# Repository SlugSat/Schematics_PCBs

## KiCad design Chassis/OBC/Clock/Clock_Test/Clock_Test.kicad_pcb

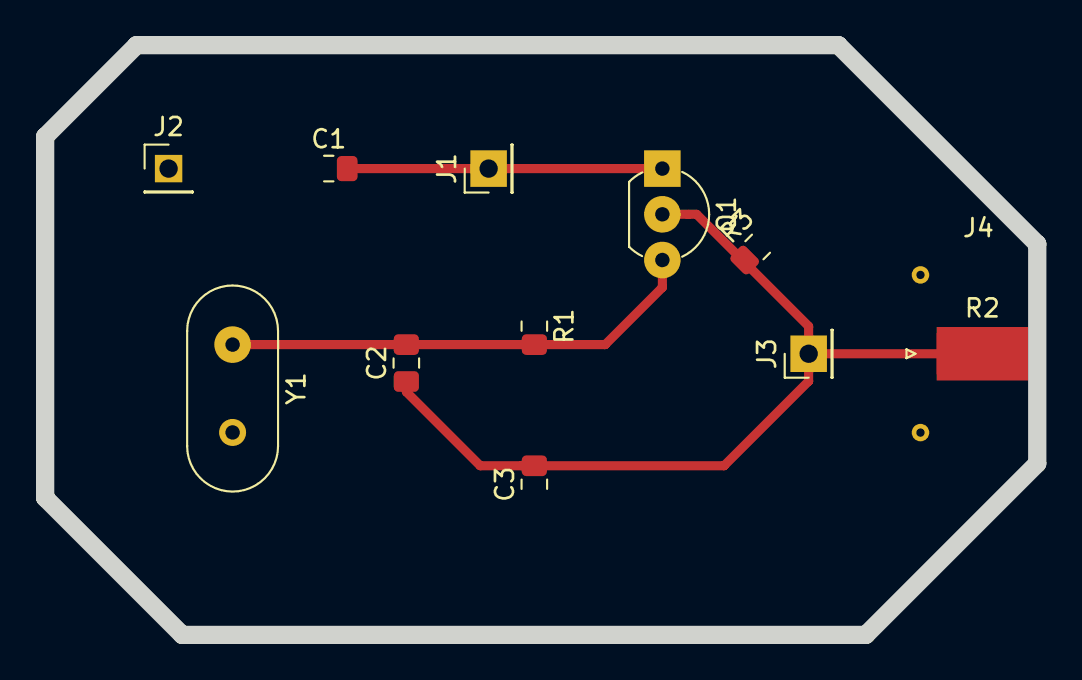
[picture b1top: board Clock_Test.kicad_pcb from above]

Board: 2 copper layers, 55.1 x 32.8 mm, 12 parts (0 on the bottom side), 4 nets.

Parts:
C1: 100 nF; C_0805_2012Metric_Pad1.15x1.40mm_HandSolder
C2: 33 pF; C_0805_2012Metric_Pad1.15x1.40mm_HandSolder
C3: 56 pF; C_0805_2012Metric_Pad1.15x1.40mm_HandSolder
J1: +1V8; PinHeader_1x01_P2.54mm_Vertical
J2, J3: Conn_01x01_Male; PinHeader_1x01_P2.54mm_Vertical
J4: Conn_Coaxial; SMA_Molex_73251-1153_EdgeMount_Horizontal
Q1: Q_NJFET_DSG; TO-92_Inline_Wide
R1: 1 M; R_0805_2012Metric_Pad1.15x1.40mm_HandSolder
R2: 50Oμs
R3: 1k; R_0805_2012Metric_Pad1.15x1.40mm_HandSolder
Y1: 10 MHz; Crystal_HC49-4H_Vertical

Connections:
/Gate: C2.2, Q1.3, R1.2, Y1.1
/Output: C2.1, C3.2, J3.1, J4.1, Q1.2, R2.1, R3.1
GND: C1.1, C3.1, J2.1, J4.2, R1.1, R3.2, Y1.2
unnamed: C1.2, J1.1, Q1.1

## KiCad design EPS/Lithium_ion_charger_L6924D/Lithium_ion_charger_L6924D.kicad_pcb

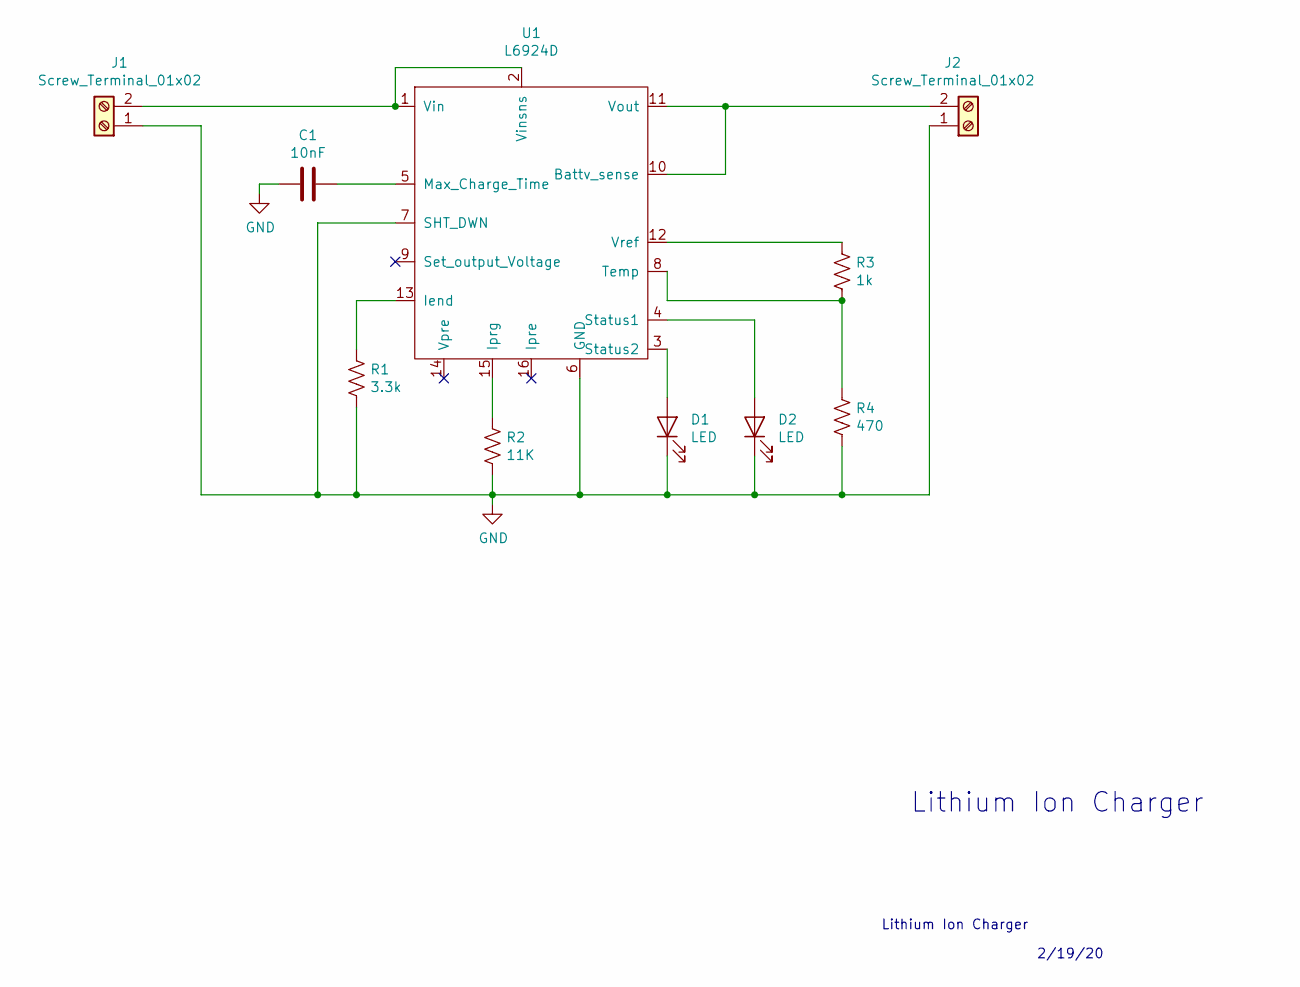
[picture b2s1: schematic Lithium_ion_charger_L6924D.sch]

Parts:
C1: 10nF; C_0805_2012Metric_Pad1.15x1.40mm_HandSolder
D1, D2: LED; LED_D5.0mm
J1: Screw_Terminal_01x02; TerminalBlock_RND_205-00287_1x02_P5.08mm_Horizontal
J2: Screw_Terminal_01x02; TerminalBlock_RND_205-00232_1x02_P5.08mm_Horizontal
R1: 3.3k; R_0805_2012Metric
R2: 11K; R_0805_2012Metric
R3: 1k; R_0805_2012Metric
R4: 470; R_0805_2012Metric
U1: L6924D; VFQFPN16

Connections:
GND: C1.2, D1.1 (K), D2.1 (K), J1.1, J2.1, R1.2, R2.2, R4.2, U1.6 (GND), U1.7 (SHT_DWN)
unnamed: C1.1, U1.5 (Max_Charge_Time)
unnamed: D1.2 (A), U1.3 (Status2)
unnamed: D2.2 (A), U1.4 (Status1)
unnamed: J1.2, U1.1 (Vin), U1.2 (Vinsns)
unnamed: J2.2, U1.10 (Battv_sense), U1.11 (Vout)
unnamed: R1.1, U1.13 (Iend)
unnamed: R2.1, U1.15 (Iprg)
unnamed: R3.1, U1.12 (Vref)
unnamed: R3.2, R4.1, U1.8 (Temp)

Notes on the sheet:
Lithium Ion Charger
2/19/20

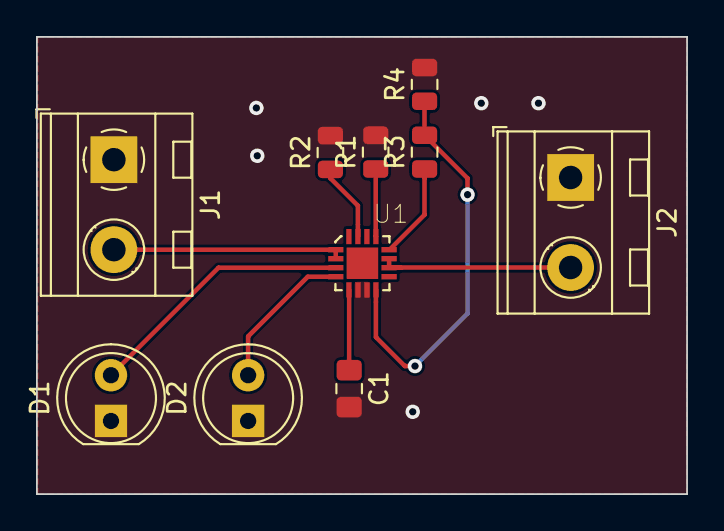
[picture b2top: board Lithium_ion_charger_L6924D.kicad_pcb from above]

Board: 2 copper layers, 36.1 x 25.4 mm, 10 parts (0 on the bottom side), 10 nets.

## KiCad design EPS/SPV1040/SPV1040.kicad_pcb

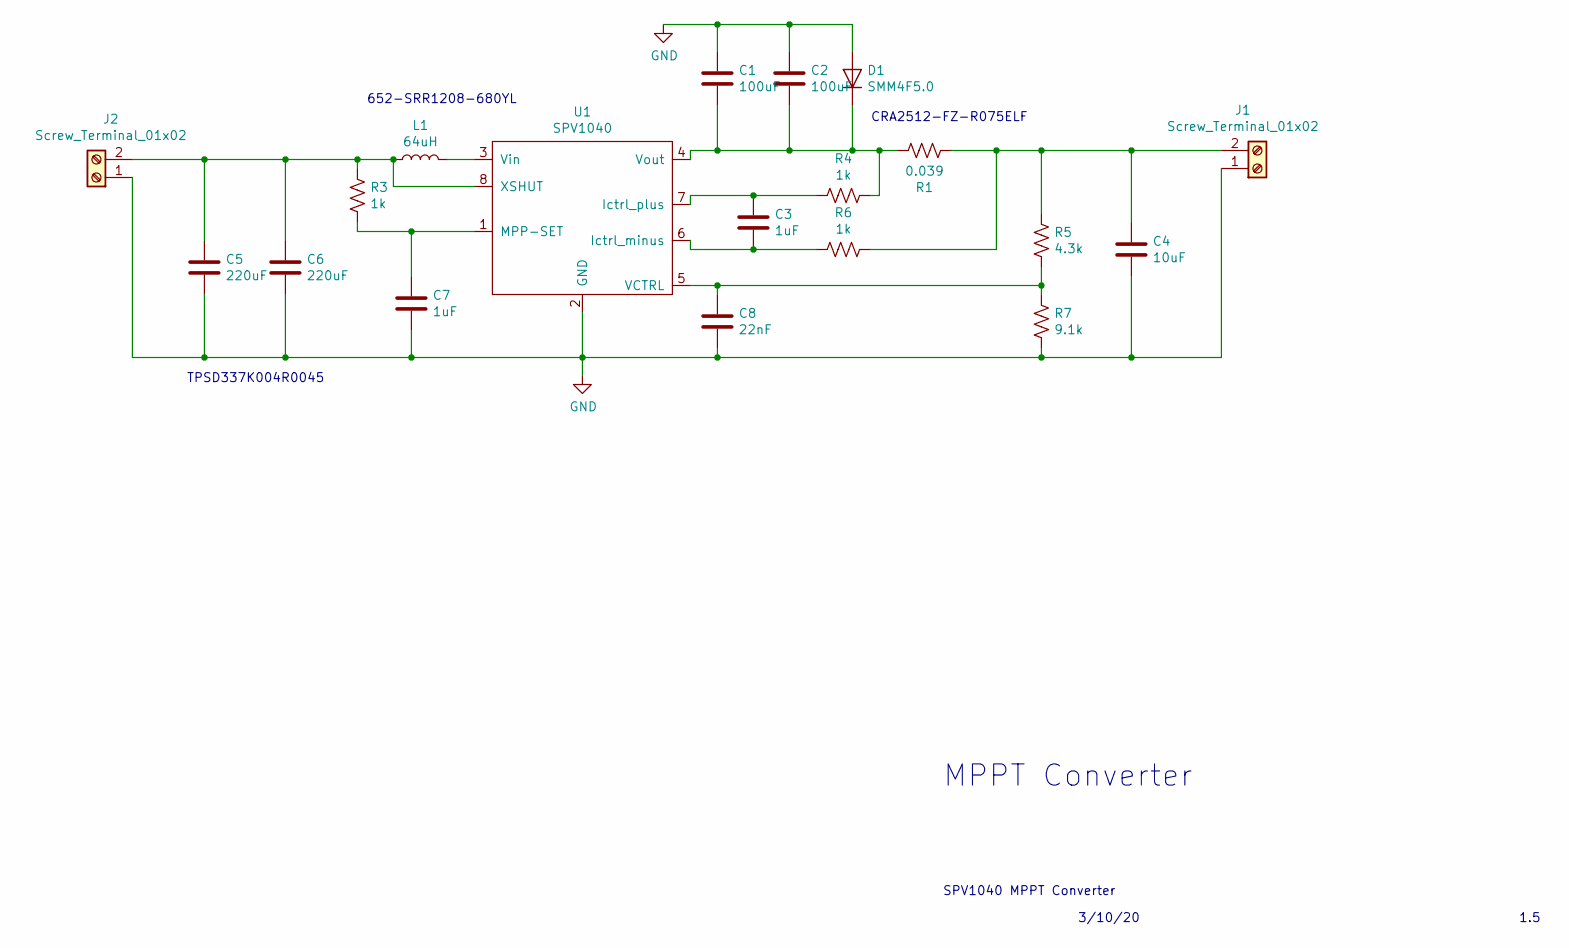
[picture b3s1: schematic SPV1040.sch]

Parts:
C1, C2: 100uF; C_1210_3225Metric_Pad1.42x2.65mm_HandSolder
C3, C7: 1uF; C_0805_2012Metric_Pad1.15x1.40mm_HandSolder
C4: 10uF; C_1210_3225Metric_Pad1.42x2.65mm_HandSolder
C5, C6: 220uF; C_2816_7142Metric_Pad3.20x4.45mm_HandSolder
C8: 22nF; C_0805_2012Metric_Pad1.15x1.40mm_HandSolder
D1: SMM4F5.0; DIO_SMM4F5.0A-TR
J1, J2: Screw_Terminal_01x02; TerminalBlock_MetzConnect_Type094_RT03502HBLU_1x02_P5.00mm_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
L1: 64uH; 652-SRR1208-680KL
R1: 0.039; CRA2512
R3, R4, R6: 1k; R_0805_2012Metric_Pad1.15x1.40mm_HandSolder
R5: 4.3k; R_0805_2012Metric_Pad1.15x1.40mm_HandSolder
R7: 9.1k; R_0805_2012Metric_Pad1.15x1.40mm_HandSolder
U1: SPV1040; TSSOP-8_W4.4mm

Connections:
GND: C1.1, C2.1, C4.2, C5.2, C6.2, C7.2, C8.2, D1.2 (A), J1.1, J2.1, R7.2, U1.2 (GND)
unnamed: C1.2, C2.2, D1.1 (K), R1.1, R4.1, U1.4 (Vout)
unnamed: C3.1, R4.2, U1.7 (Ictrl_plus)
unnamed: C3.2, R6.2, U1.6 (Ictrl_minus)
unnamed: C4.1, J1.2, R1.2, R5.1, R6.1
unnamed: C5.1, C6.1, J2.2, L1.1, R3.1, U1.8 (XSHUT)
unnamed: C7.1, R3.2, U1.1 (MPP-SET)
unnamed: C8.1, R5.2, R7.1, U1.5 (VCTRL)
unnamed: L1.2, U1.3 (Vin)

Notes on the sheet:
SPV1040 MPPT Converter
3/10/20
1.5
MPPT Converter
652-SRR1208-680YL
CRA2512-FZ-R075ELF
TPSD337K004R0045

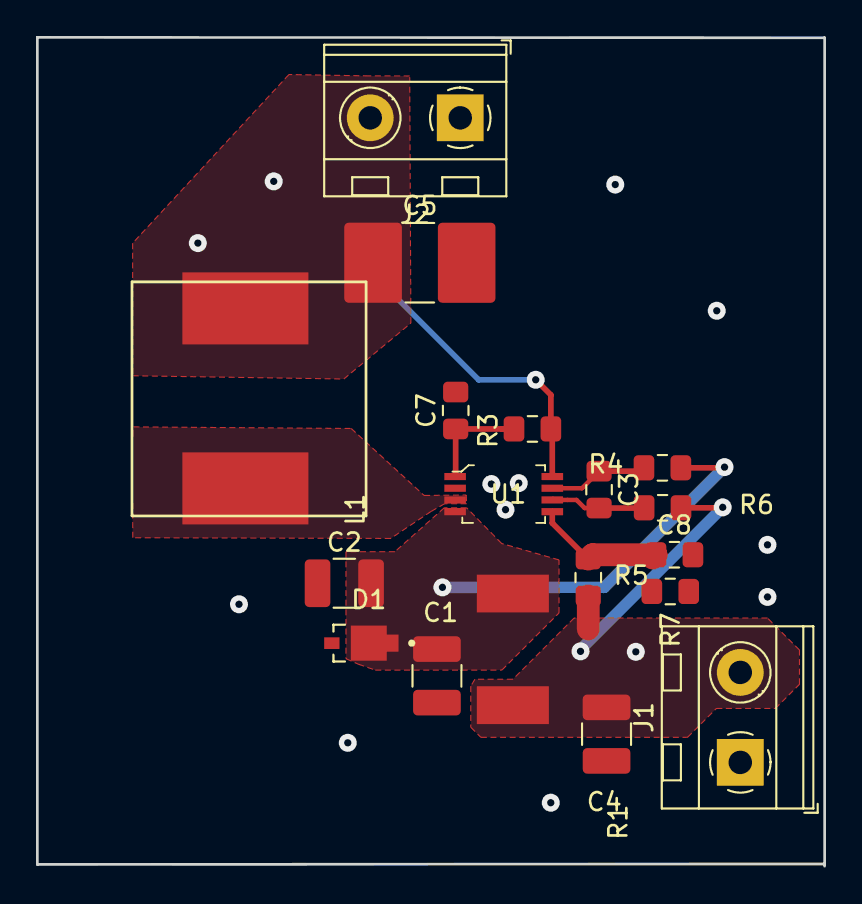
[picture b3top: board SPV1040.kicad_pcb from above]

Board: 2 copper layers, 43.7 x 46.1 mm, 19 parts (1 on the bottom side), 9 nets.

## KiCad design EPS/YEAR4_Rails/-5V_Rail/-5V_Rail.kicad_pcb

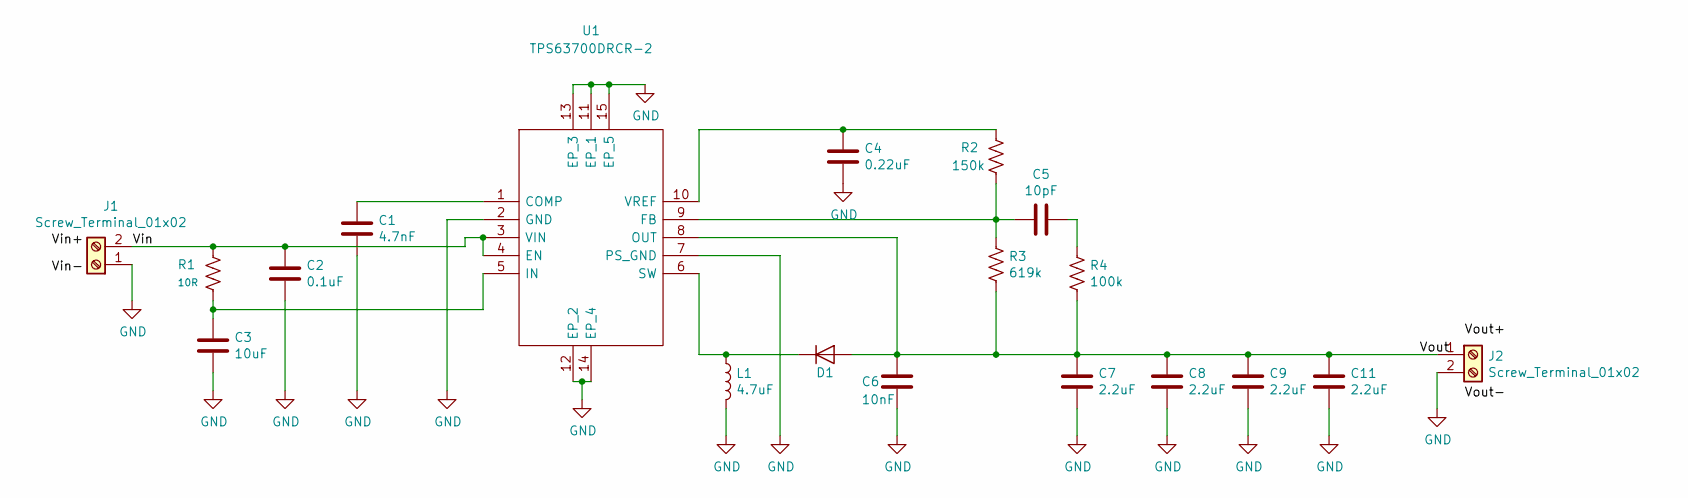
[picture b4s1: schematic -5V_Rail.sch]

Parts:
C1: 4.7nF; C_0805_2012Metric_Pad1.15x1.40mm_HandSolder
C2: 0.1uF; C_0805_2012Metric_Pad1.15x1.40mm_HandSolder
C3: 10uF; C_0805_2012Metric_Pad1.15x1.40mm_HandSolder
C4: 0.22uF; C_0805_2012Metric_Pad1.15x1.40mm_HandSolder
C5: 10pF; C_0805_2012Metric_Pad1.15x1.40mm_HandSolder
C6: 10nF; C_0805_2012Metric_Pad1.15x1.40mm_HandSolder
C7, C8, C9, C11: 2.2uF; C_0805_2012Metric_Pad1.15x1.40mm_HandSolder
D1: D; SODFL3718X108N
J1, J2: Screw_Terminal_01x02; TerminalBlock_MetzConnect_Type094_RT03502HBLU_1x02_P5.00mm_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
L1: 4.7uF; L_Coilcraft_LPS4018
R1: 10R; R_0805_2012Metric_Pad1.15x1.40mm_HandSolder
R2: 150k; R_0805_2012Metric_Pad1.15x1.40mm_HandSolder
R3: 619k; R_0805_2012Metric_Pad1.15x1.40mm_HandSolder
R4: 100k; R_0805_2012Metric_Pad1.15x1.40mm_HandSolder
U1: TPS63700DRCR-2; TPS63700DRCR_copy; Mouser Part Number 595-TPS63700DRCR

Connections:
/Vin: C2.1, J1.2, R1.1, U1.3 (VIN), U1.4 (EN)
/Vout: C6.1, C7.1, C8.1, C9.1, C11.1, D1.2 (A), J2.1, R3.2, R4.2, U1.8 (OUT)
GND: C1.2, C2.2, C3.2, C4.2, C6.2, C7.2, C8.2, C9.2, C11.2, J1.1, J2.2, L1.2, U1.2 (GND), U1.7 (PS_GND), U1.11 (EP_1), U1.12 (EP_2), U1.13 (EP_3), U1.14 (EP_4), U1.15 (EP_5)
unnamed: C1.1, U1.1 (COMP)
unnamed: C3.1, R1.2, U1.5 (IN)
unnamed: C4.1, R2.1, U1.10 (VREF)
unnamed: C5.1, R4.1
unnamed: C5.2, R2.2, R3.1, U1.9 (FB)
unnamed: D1.1 (K), L1.1, U1.6 (SW)

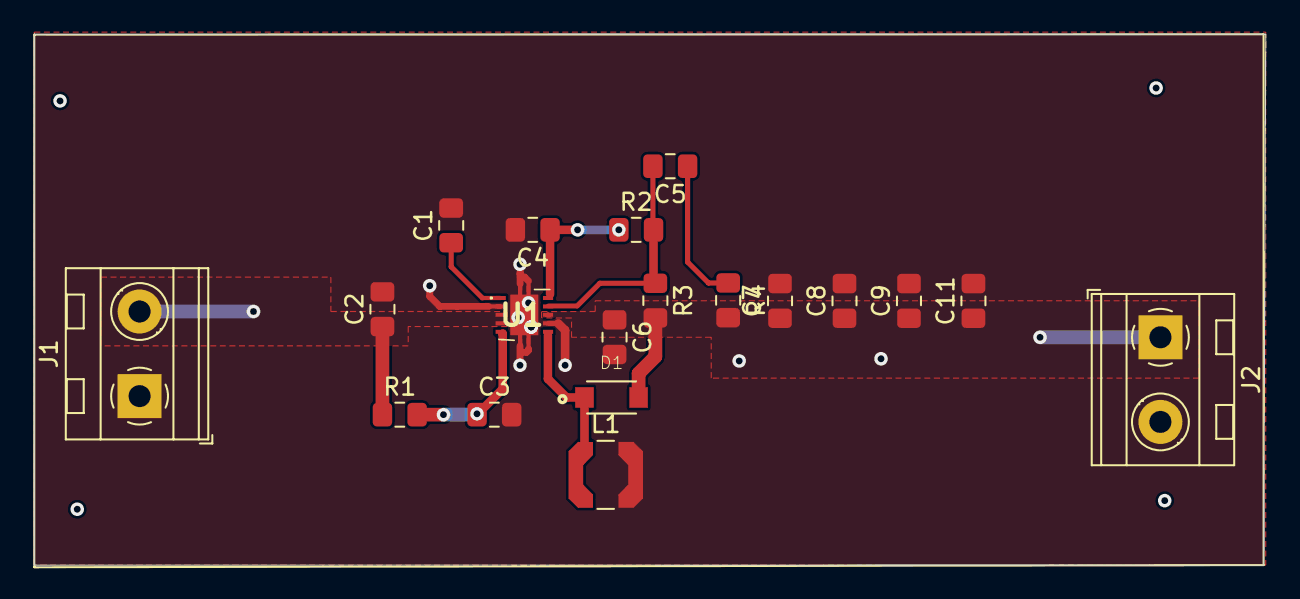
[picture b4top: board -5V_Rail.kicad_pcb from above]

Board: 2 copper layers, 72.8 x 31.4 mm, 19 parts (0 on the bottom side), 9 nets.

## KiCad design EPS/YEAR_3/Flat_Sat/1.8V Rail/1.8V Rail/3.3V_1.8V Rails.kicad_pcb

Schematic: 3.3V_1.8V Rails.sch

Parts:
Bypass1, Bypass2: 1uF; C_0805_2012Metric_Pad1.15x1.40mm_HandSolder
C1, C3, C6: 1u; C_0805_2012Metric_Pad1.15x1.40mm_HandSolder
C2: 47u; C_0805_2012Metric_Pad1.15x1.40mm_HandSolder
C4: 3.3n; C_0805_2012Metric_Pad1.15x1.40mm_HandSolder
C5: 100u; C_0805_2012Metric_Pad1.15x1.40mm_HandSolder
C7: 0.1u; C_0805_2012Metric_Pad1.15x1.40mm_HandSolder
J1: Battery; TerminalBlock_MetzConnect_Type094_RT03502HBLU_1x02_P5.00mm_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
J2: SCL; PinHeader_1x01_P2.54mm_Vertical
J3: SDA; PinHeader_1x01_P2.54mm_Vertical
J4: Enable; PinHeader_1x01_P2.54mm_Vertical
J5: GND; PinHeader_1x01_P2.54mm_Vertical
J6: Flag; PinHeader_1x01_P2.54mm_Vertical
J7, J8: Screw_Terminal_01x02; TerminalBlock_MetzConnect_Type094_RT03502HBLU_1x02_P5.00mm_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
L1: 22u; IND_SRP6540-100M
R1, R3, R4: 10; R_0805_2012Metric_Pad1.15x1.40mm_HandSolder
R2: 39m; R_Shunt_Ohmite_LVK12
R5, R6: 20k; R_0805_2012Metric_Pad1.15x1.40mm_HandSolder
R_PullUp1: 10k; R_0805_2012Metric_Pad1.15x1.40mm_HandSolder
R_Set1: x; R_0805_2012Metric_Pad1.15x1.40mm_HandSolder
U1: LM2852
U2: INA226; MSOP-10_3x3mm_P0.5mm
U3: MAX4995A; SOT-23-6_Handsoldering

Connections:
+3V3: C7.2, J8.1, R5.1, R6.1, R_PullUp1.1, U2.2 (A0), U2.6 (Vs)
+BATT: C1.1, C2.1, J1.2, R1.2, U1.6, U1.7
GND: Bypass1.1, Bypass2.1, C1.2, C2.2, C3.2, C4.2, C5.2, C7.1, J1.1, J5.1, J7.2, J8.2, R_Set1.2, U1.3, U1.10, U1.11, U1.15, U2.1 (A1), U2.7 (GND), U3.2
unnamed: Bypass1.2, R2.1, U2.8 (Vbus), U3.5
unnamed: Bypass2.2, J7.1, U3.1
unnamed: C3.1, R1.1, U1.1
unnamed: C4.1, U1.4
unnamed: C5.1, L1.2, R2.4, U1.14
unnamed: C6.1, R3.1, U2.10 (Vin+)
unnamed: C6.2, R4.1, U2.9 (Vin-)
unnamed: J2.1, R5.2, U2.5 (SCL)
unnamed: J3.1, R6.2, U2.4 (SDA)
unnamed: J4.1, U3.4
unnamed: J6.1, R_PullUp1.2, U3.6
unnamed: L1.1, U1.8, U1.9
unnamed: R2.2, R4.2
unnamed: R2.3, R3.2
unnamed: R_Set1.1, U3.3

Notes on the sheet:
Buck Converter
Current Sensor
1.8V Rail
C1-C4, C6 are ceramic caps
J4) Enable from uP J5) uP GND J6) Flag Output to uP
Protected Output
3.3V Pullup Source
Power Switch (1.8V, 3.3V, 5V)
Current Setpoint
Slave Address = 1000001

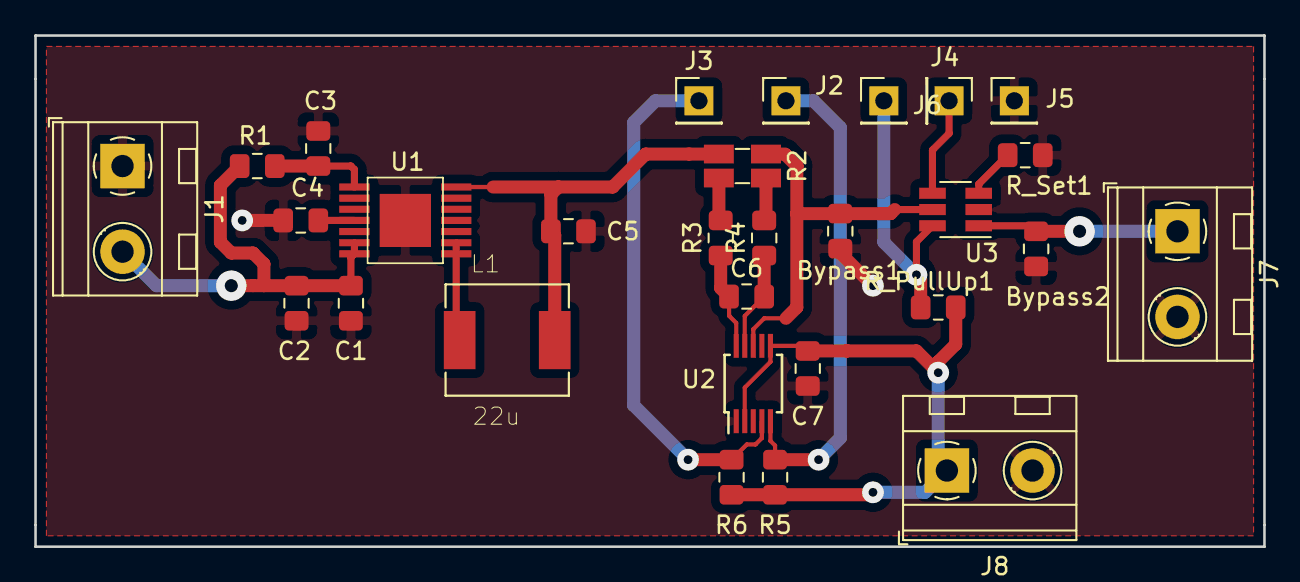
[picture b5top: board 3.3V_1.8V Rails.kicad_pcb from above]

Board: 2 copper layers, 71.8 x 29.8 mm, 29 parts (0 on the bottom side), 18 nets.

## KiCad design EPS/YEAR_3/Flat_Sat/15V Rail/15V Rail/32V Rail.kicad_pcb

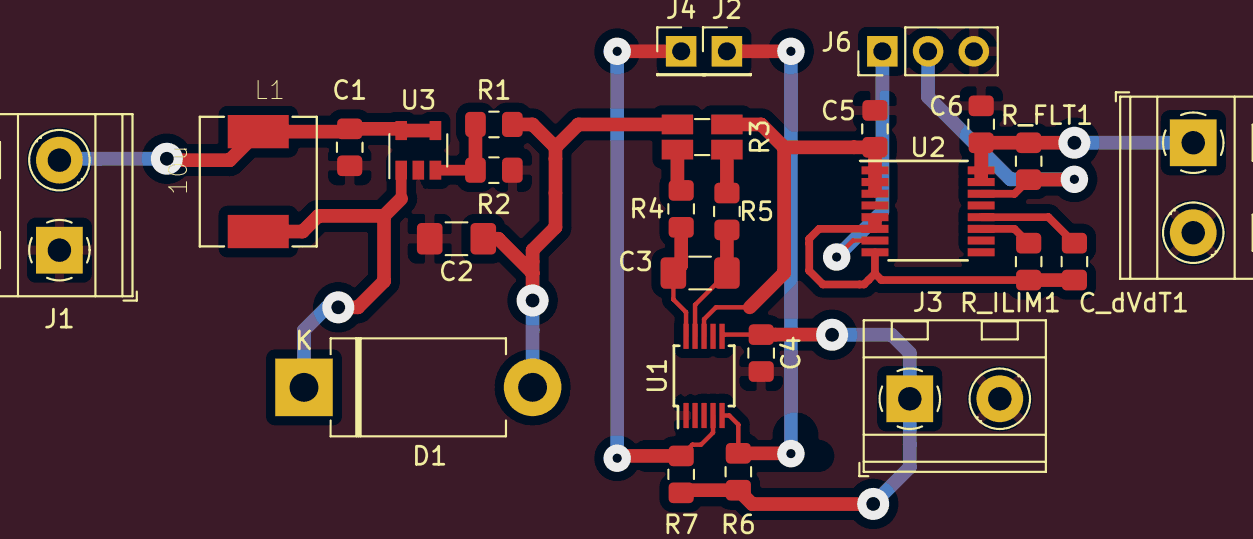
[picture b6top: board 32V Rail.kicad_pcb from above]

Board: 2 copper layers, 27 parts (0 on the bottom side), 19 nets.

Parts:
C1: 10u; C_0805_2012Metric_Pad1.15x1.40mm_HandSolder
C2: 47u; C_1206_3216Metric_Pad1.42x1.75mm_HandSolder
C3: 1u; C_1206_3216Metric_Pad1.42x1.75mm_HandSolder
C4: 0.1u; C_0805_2012Metric_Pad1.15x1.40mm_HandSolder
C5, C6: 1uF; C_0805_2012Metric_Pad1.15x1.40mm_HandSolder
C_dVdT1: 1uF; C_0805_2012Metric_Pad1.15x1.40mm_HandSolder
D1: DIODE; D_DO-201AD_P12.70mm_Horizontal
J1: Vin; TerminalBlock_MetzConnect_Type094_RT03502HBLU_1x02_P5.00mm_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
J2: SCL; PinHeader_1x01_P2.54mm_Vertical
J3: Supply Voltage; TerminalBlock_MetzConnect_Type094_RT03502HBLU_1x02_P5.00mm_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
J4: SDA; PinHeader_1x01_P2.54mm_Vertical
J5: Screw_Terminal_01x02; TerminalBlock_MetzConnect_Type094_RT03502HBLU_1x02_P5.00mm_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
J6: Conn_01x03_Male; PinHeader_1x03_P2.54mm_Vertical
L1: 10u; IND_SRP6540-100M
R1: 1.02M; R_0805_2012Metric_Pad1.15x1.40mm_HandSolder
R2: 91k; R_0805_2012Metric_Pad1.15x1.40mm_HandSolder
R3: 39m; R_Shunt_Ohmite_LVK12
R4, R5: 6.8; R_0805_2012Metric_Pad1.15x1.40mm_HandSolder
R6, R7: 20k; R_0805_2012Metric_Pad1.15x1.40mm_HandSolder
R_FLT1: 100k; R_0805_2012Metric_Pad1.15x1.40mm_HandSolder
R_ILIM1: 12k; R_0805_2012Metric_Pad1.15x1.40mm_HandSolder
U1: INA226; MSOP-10_3x3mm_P0.5mm
U2: TPS26600; TSSOP-16_4.4x5mm_P0.65mm
U3: MCP1663; SOT-23-5

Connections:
+3V3: C4.1, J3.1, R6.1, R7.2, U1.6
+BATT: C1.1, J1.2, L1.1, U3.4, U3.5
GND: C1.2, C2.2, C4.2, C5.2, C6.1, J1.1, J3.2, J5.2, J6.3, R2.2, U1.1, U1.2, U1.7, U2.4, U2.9, U2.13, U3.2
unnamed: C2.1, D1.2, R1.1, R3.4
unnamed: C3.1, R5.2, U1.9
unnamed: C3.2, R4.2, U1.10
unnamed: C5.1, R3.1, U1.8, U2.1, U2.2, U2.3
unnamed: C6.2, J5.1, R_FLT1.1, U2.15, U2.16
unnamed: C_dVdT1.1, R_ILIM1.2, U2.5, U2.6, U2.8
unnamed: C_dVdT1.2, U2.12
unnamed: D1.1, L1.2, U3.1
unnamed: J2.1, R6.2, U1.5
unnamed: J4.1, R7.1, U1.4
unnamed: J6.1, U2.7
unnamed: J6.2, R_FLT1.2, U2.14
unnamed: R1.2, R2.1, U3.3
unnamed: R3.2, R5.1
unnamed: R3.3, R4.1
unnamed: R_ILIM1.1, U2.11
